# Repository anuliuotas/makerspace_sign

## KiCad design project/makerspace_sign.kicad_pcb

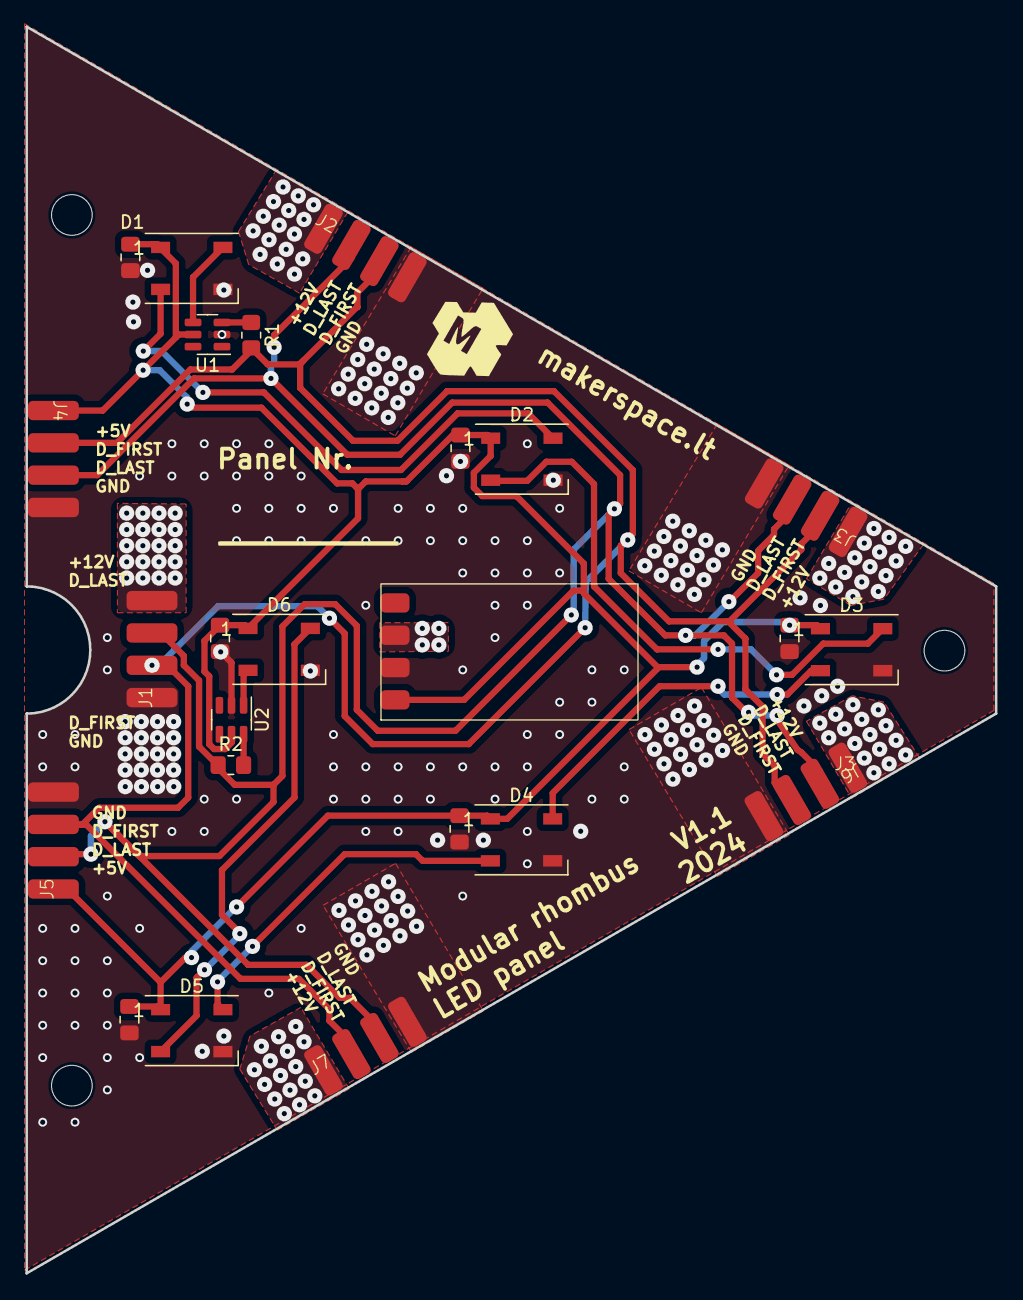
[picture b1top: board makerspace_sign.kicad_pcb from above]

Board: 2 copper layers, 76.2 x 98.0 mm, 28 parts (0 on the bottom side), 14 nets.

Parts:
Buck1: 5v buck
C1, C2, C3, C4, C5, C6: 100n; C_0805_2012Metric_Pad1.18x1.45mm_HandSolder
D1, D2, D3, D4, D5, D6: WS2812B; LED_WS2812B_PLCC4_5.0x5.0mm_P3.2mm
G1: LOGO_KMS; logo_kms_small_silkscreen
H1, H2, H3: MountingHole; MountingHole_3.2mm_M3
J1: Conn_EXT; 4_pin_solder_pad
J2: Conn_E1_M; 4_pin_solder_pad
J3: Conn_E1_F; 4_pin_solder_pad
J4: Conn_OTH_M; 4_pin_solder_pad
J5: Conn_OTH_F; 4_pin_solder_pad
J6: Conn_E2_F; 4_pin_solder_pad
J7: Conn_E2_M; 4_pin_solder_pad
R1, R2: R; R_0805_2012Metric_Pad1.20x1.40mm_HandSolder
U1, U2: USBLC6-2SC6; SOT-23-6

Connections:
+5V: Buck1.1 (VO+), C1.1, C2.1, C3.1, C4.1, C5.1, C6.1, D1.1 (VDD), D2.1 (VDD), D3.1 (VDD), D4.1 (VDD), D5.1 (VDD), D6.1 (VDD), J4.1, J5.1, U1.5 (VBUS), U2.5 (VBUS)
+12V: Buck1.3 (IN+), J1.4, J2.1, J3.1, J6.1, J7.1
/D_12: D1.2 (DOUT), D2.4 (DIN)
/D_23: D2.2 (DOUT), D3.4 (DIN)
/D_34: D3.2 (DOUT), D4.4 (DIN)
/D_45: D4.2 (DOUT), D5.4 (DIN)
/D_56: D5.2 (DOUT), D6.4 (DIN)
/D_FIRST: J1.2, J2.3, J3.2, J4.2, J5.3, J6.3, J7.2, R1.2
/D_LAST: J1.3, J2.2, J3.3, J4.3, J5.2, J6.2, J7.3, R2.1
GND: Buck1.2 (GND), C1.2, C2.2, C3.2, C4.2, C5.2, C6.2, D1.3 (VSS), D2.3 (VSS), D3.3 (VSS), D4.3 (VSS), D5.3 (VSS), D6.3 (VSS), J1.1, J2.4, J3.4, J4.4, J5.4, J6.4, J7.4, U1.2 (GND), U2.2 (GND)
unnamed: D1.4 (DIN), U1.4 (I/O2)
unnamed: D6.2 (DOUT), U2.1 (I/O1)
unnamed: R1.1, U1.3 (I/O2)
unnamed: R2.2, U2.6 (I/O1)

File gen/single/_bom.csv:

"Row","Description","Part","References","Value","Footprint","Quantity Per PCB","Status","Datasheet"
"1","","5v_buck","Buck1","~","5v buck","1"," ",""
"2","Unpolarized capacitor","C","C1,C2,C3,C4,C5,C6","100n","C_0805_2012Metric_Pad1.18x1.45mm_HandSolder","6"," ","~"
"3","RGB LED with integrated controller","WS2812B","D1,D2,D3,D4,D5,D6","WS2812B","LED_WS2812B_PLCC4_5.0x5.0mm_P3.2mm","6"," ","https://cdn-shop.adafruit.com/datasheets/WS2812B.pdf"
"4","","LOGO_KMS","G1","LOGO_KMS","logo_kms_small_silkscreen","1"," ",""
"5","Generic connector, single row, 01x04, script generated","Conn_01x04_Socket","J3,J5,J7","Conn_E1_F","4_pin_solder_pad","3"," ","~"
"6","Generic connector, single row, 01x04, script generated","Conn_01x04_Pin","J1,J2,J4,J6","Conn_EXT","4_pin_solder_pad","4"," ","~"

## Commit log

2024-04-22 fixed gen
2024-04-24 v2 gen
2024-05-24 prieš perdaryma
